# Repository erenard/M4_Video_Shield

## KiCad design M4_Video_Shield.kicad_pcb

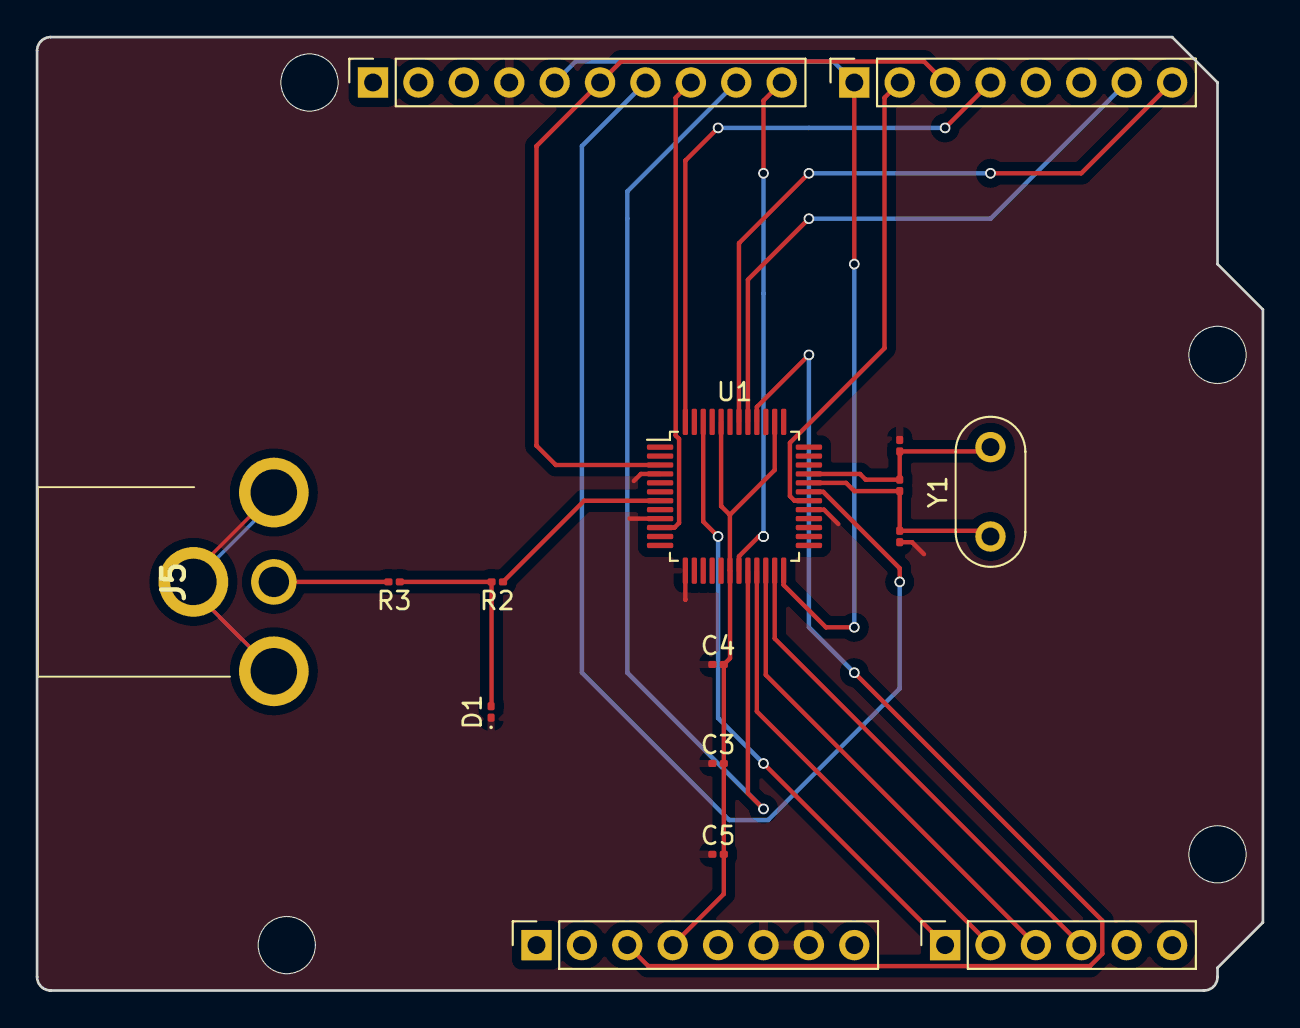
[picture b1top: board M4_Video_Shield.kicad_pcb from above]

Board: 2 copper layers, 68.6 x 53.3 mm, 20 parts (0 on the bottom side), 22 nets.

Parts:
C1, C2: 10pF; C_0201_0603Metric
C3, C4: 100nF; C_0201_0603Metric
C5: 10uF; C_0201_0603Metric
D1: CG0603MLA; D_0201_0603Metric
J1: Power; PinSocket_1x08_P2.54mm_Vertical
J2: Digital/PWM; PinSocket_1x10_P2.54mm_Vertical
J3: Analog; PinSocket_1x06_P2.54mm_Vertical
J4: Digital/PWM; PinSocket_1x08_P2.54mm_Vertical
J5: Video Out; RCJ014
MH1, MH2, MH3, MH4: MountingHole_3.2mm
R1: 1M; R_0201_0603Metric
R2, R3: 22; R_0201_0603Metric
U1: VS23S010D; LQFP-48_7x7mm_P0.5mm
Y1: 4.433618MHz; Resonator-2Pin_W8.0mm_H3.5mm

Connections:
+3V3: C3.2, C4.2, C5.2, J1.4, U1.18 (VCC0), U1.38 (VCC1), U1.44 (VCC2)
/4: J4.4, U1.48 (XCS)
/8: J2.10, U1.19 (PIO5)
/13: J2.5, J4.1, U1.24 (SI/IO0)
/*5: J2.6, J4.3, U1.3 (SO/IO1)
/*6: J4.2, U1.30 (SCLK)
/*9: J2.9, U1.20 (PIO4)
/*10: J2.8, U1.10 (XWP/IO2)
/*11: J2.7, U1.31 (XHOLD/IO3)
/A0: J3.1, U1.46 (MVBLK_#0)
/A1: J3.2, U1.21 (XCSPAR)
/A2: J3.3, U1.22 (XRD)
/A3: J3.4, U1.23 (XWR)
/PA22: J4.7, U1.41 (PIO6)
/PA23: J4.8, U1.42 (PIO7)
/VideoOut0: R2.1, U1.7 (VideoOut_#0)
/XtalIn: C1.2, R1.1, U1.32 (VXTALIN), Y1.1
/XtalOut: C2.2, R1.2, U1.33 (VXTALOUT), Y1.2
/~RESET: J1.3, U1.40 (XRESET)
GND: C1.1, C2.1, C3.1, C4.1, C5.1, D1.1 (A1), J1.6, J1.7, J2.4, U1.4 (GND0), U1.9 (GND1), U1.13 (GND2), U1.29 (GND3), U1.47 (GND4)
unnamed: D1.2 (A2), R2.2, R3.1
unnamed: J5.1 (In), R3.2

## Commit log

2023-07-07 Route PCB
